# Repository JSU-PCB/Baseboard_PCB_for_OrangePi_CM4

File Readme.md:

# Baseboard PCB for OrangePi CM4

## 📌 Project Overview
This project documents the design and development of a custom baseboard for the Orange Pi CM4 compute module. It serves as a practical reference for a complete hardware design workflow, from initial schematic capture to PCB layout and manufacturing output. The goal is to share the experience and methodology of building a functional, production‑ready baseboard.

The project is developed in KiCad and cross‑referenced with Altium Designer for validation and advanced analysis. Both tools are used to ensure a comprehensive and reliable design flow.

## ⚠️ Disclaimer
This project is provided **"as is"** for educational and experimental purposes only. No warranty or guarantee is made regarding the correctness, completeness, or safety of the design. The authors accept **no responsibility or liability** for any damages, data loss, or injuries resulting from the use, assembly, or manufacture of this design. Users are solely responsible for verifying the suitability and accuracy of the design for their specific applications.

## 🔧 Contribution
Contributions are welcome! If you find a bug, have a suggestion, or want to help improve the design, please open an **Issue** or submit a **Pull Request**. All contributions must comply with the project's license and code of conduct.

## 📜 License
This hardware design is released under the **CERN Open Hardware Licence Version 2 – Permissive (CERN-OHL-P-2.0)**.  
You are free to use, study, modify, and distribute the design, provided you retain the copyright notice and disclaimer. Commercial use is permitted without the obligation to share proprietary modifications, though we encourage sharing improvements with the community.

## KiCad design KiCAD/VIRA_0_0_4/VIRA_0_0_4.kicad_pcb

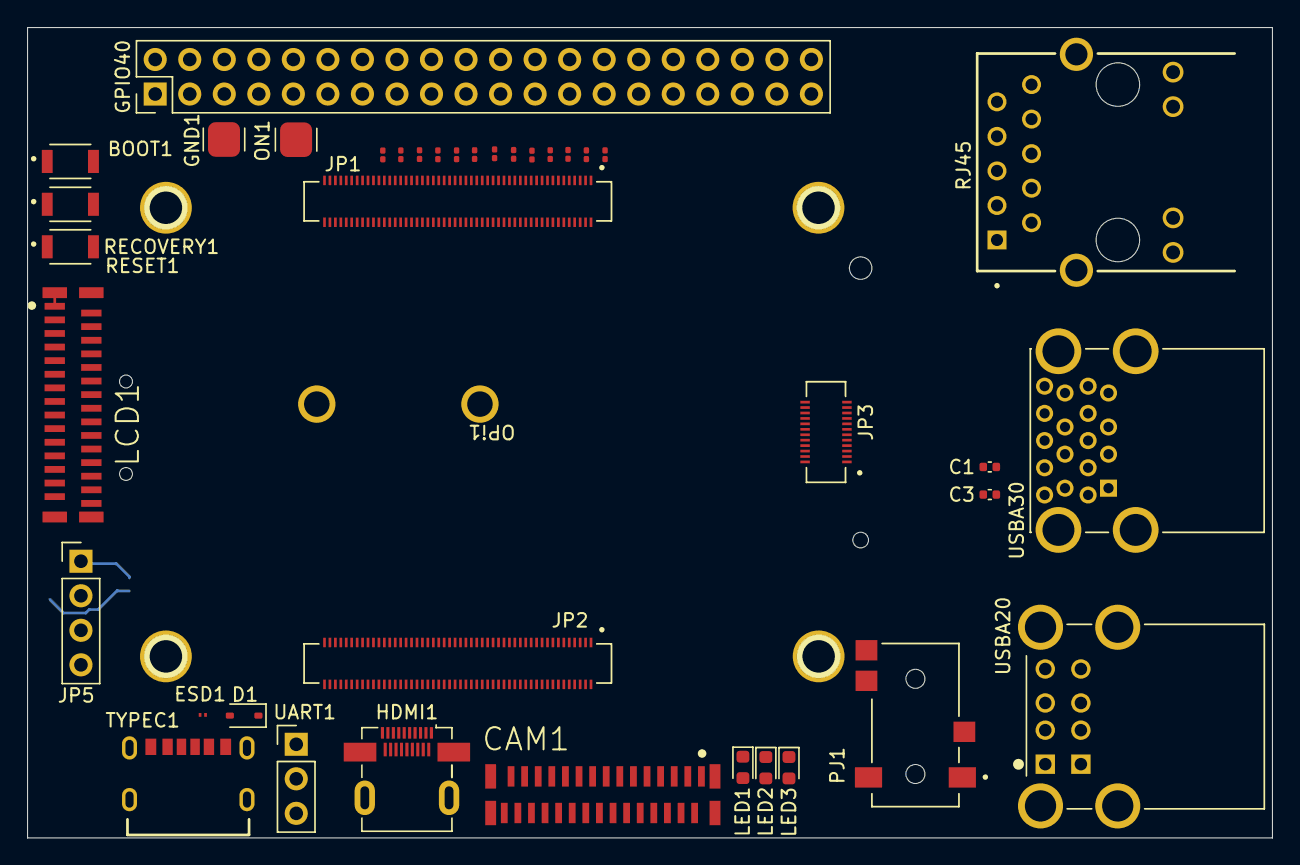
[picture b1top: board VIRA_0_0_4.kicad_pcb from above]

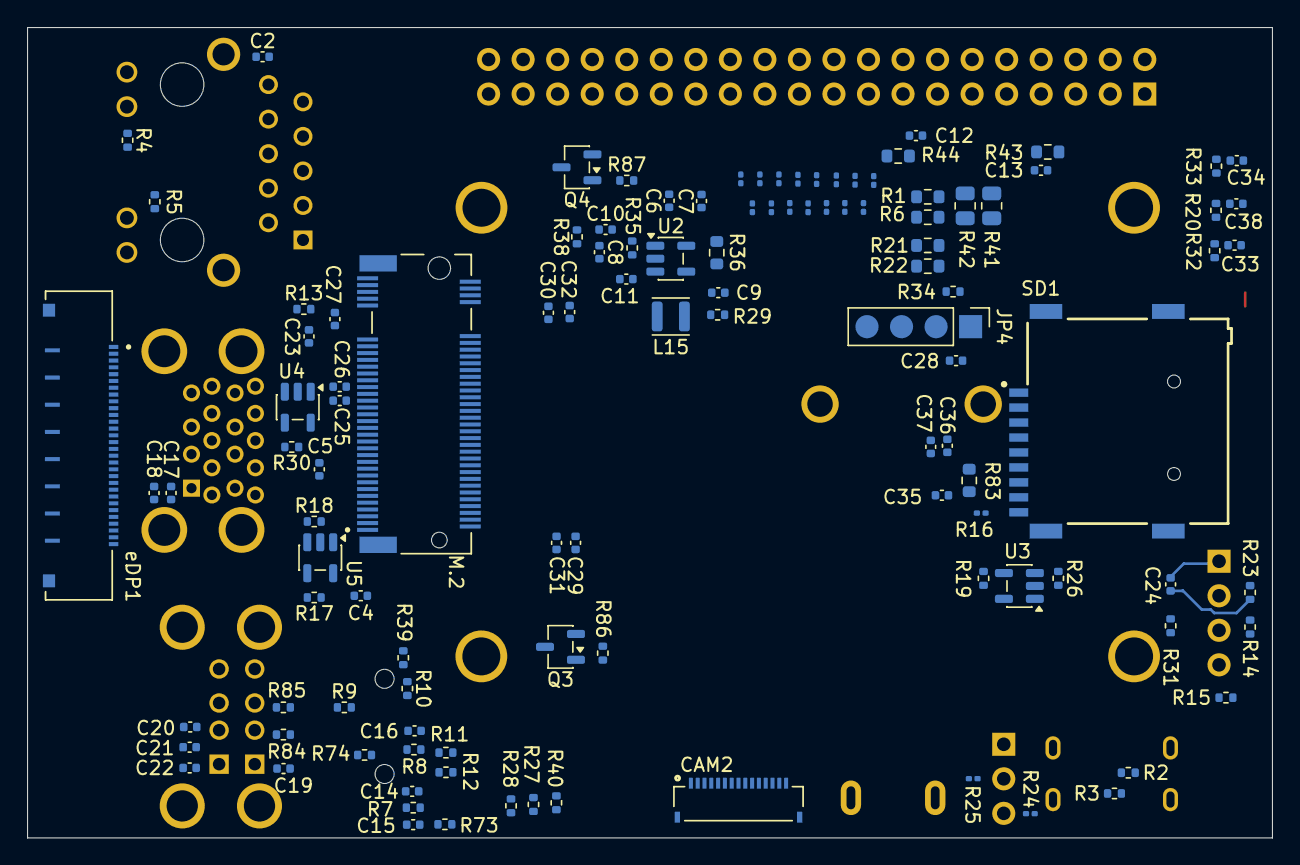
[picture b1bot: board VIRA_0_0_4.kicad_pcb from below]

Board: 6 copper layers, 91.6 x 59.6 mm, 153 parts (113 on the bottom side), 207 nets.

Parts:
BOOT1: SW_Omron_B3FS; SW_B3U-1000P
C1, C2, C3, C4, C5, C7, C8, C10, C15, C16, C18, C20, C22, C25, C26, C27, C31, C32, C33, C34, C35, C37, C38: 100nF; C_0402_1005Metric
C6, C11, C12, C13, C14, C17, C19, C21, C23, C24, C28, C29, C30, C36: 10uF; C_0402_1005Metric
C9: 22pF; C_0402_1005Metric
CAM1: FH12-30S-0.5SVA_54_; HIROSE_FH12-30S-0.5SVA
CAM2: FH19C-15S-0.5SH_10_; HRS_FH19C-15S-0.5SH_10_
D1: 1N5819; D_SOD-323
ESD1: PESD5V0H1BSFYL; DIO_PESD5V0H1BSFYL
GND1: GND; Pad
GPIO40: MTLW-120-06-G-D-160; PinHeader_2x20_P2.54mm_Vertical
HDMI1: 467652301; HDMI_Micro-D_Molex_46765-2xxx
JP1, JP2: DF40C-100DS-0.4V_51_; HIROSE_DF40C-100DS-0.4V_51_
JP3: DF40C-24DS-0.4V_51_; HIROSE_DF40C-24DS-0.4V_51_
JP4: HEADER 4; Pad SMD 1x4
JP5: HEADER 4; PinHeader_1x04_P2.54mm_Vertical
L15: 2.2uH; L_Wuerth_PMCI-252012
LCD1: FH12-30S-0.5SVA_54_; HIROSE_FH12-30S-0.5SVA
LED1: LED_RED; LED_0603_1608Metric
LED2: LED_GREEN; LED_0603_1608Metric
LED3: LED_BLUE; LED_0603_1608Metric
M.2: MDT420M03001; AMPHENOL_MDT420M03001
ON1: ON; Pad
OPi1: OpiCM4
PJ1: SJ2-35894B-SMT-TR; CUI_SJ2-35894B-SMT-TR
Q3, Q4: 2SK3018; SOT-23-3
R1, R6, R21: NC 0R; R_0603_1608Metric
R2, R3, R39: 5.1K; R_0402_1005Metric
R4, R5, R9, R10, R27, R28: 470R; R_0402_1005Metric
R7, R11, R73: 100K; R_0402_1005Metric
R8, R15, R23, R33, R34: 0R; R_0402_1005Metric
R12, R20, R32: 22R; R_0402_1005Metric
R13, R18, R26: 6K8; R_0402_1005Metric
R14, R31: 10K; R_0402_1005Metric
R16, R24, R25, R45, R46, R47, R49, R50, R54, R55, R56, R57, R59, R60, R61, R63, R64, R65, R66, R67, R68, R69, R70: 200R; R_0201_0603Metric
R17, R19, R30, R38: NC 10K; R_0402_1005Metric
R22, R36, R43, R44: 0R; R_0603_1608Metric
R29: 232K; R_0402_1005Metric
R35: 49.9K; R_0402_1005Metric
R40: 2K2; R_0402_1005Metric
R41, R42: 0R; R_0805_2012Metric
R48, R51, R52, R53, R58, R62, R71, R72: 47R; R_0201_0603Metric
R74: 2.2K; R_0402_1005Metric
R83: 1K; R_0603_1608Metric
R84, R85: 2R2; R_0402_1005Metric
R86, R87: 33K; R_0402_1005Metric
RECOVERY1: SW_Omron_B3FS; SW_B3U-1000P
RESET1: SW_Omron_B3FS; SW_B3U-1000P
RJ45: MGC005-2CD2C001H_REVA; GCT_MGC005-2CD2C001H_REVA
SD1: MEM2075-00-140-01-A; GCT_MEM2075-00-140-01-A
TYPEC1: USB4125-GF-A_REVA2; GCT_USB4125-GF-A_REVA2
U2: ETA3409/SY8089AAC; SOT-23-5
U3, U4, U5: SGM2590D; SOT-23-5
UART1: Conn_01x03; PinHeader_1x03_P2.54mm_Vertical
USBA20: USB_HOST; TE_5787745-2
USBA30: SS-52000-003; STEWART_SS-52000-003
eDP1: FH63S-30S-0.5SH; HRS_FH63S-30S-0.5SH

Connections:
/Page_3/CC1: R2.1, TYPEC1.A5 (CC1)
/Page_3/CC2: R3.1, TYPEC1.B5 (CC2)
BOOT-SW: JP1.93, R33.2
BT_nDIS: JP1.91, R6.2
CAMERA_PDN_L: CAM1.$21 (21), CAM1.$22 (22), CAM2.11, JP1.97
DIY_LED: JP1.21, eDP1.8
EDP_TX_AUXN: JP2.66, eDP1.21
EDP_TX_AUXP: JP2.64, eDP1.22
EDP_TX_D0N: JP2.60, eDP1.25
EDP_TX_D0P: JP2.58, eDP1.24
EDP_TX_D1N: JP2.54, eDP1.28
EDP_TX_D1P: JP2.52, eDP1.27
GND: BOOT1.2, C2.1, C4.2, C5.2, C6.2, C7.2, C8.2, C10.2, C11.2, C12.2, C13.2, C14.1, C15.2, C16.2, C17.2, C18.2, C19.2, C20.2, C21.2, C22.2, C23.2, C24.2, C27.2, C28.2, C29.2, C30.2, C31.2, C32.2, C33.2, C34.2, C35.2, C36.2, C37.2, C38.2, CAM1.31 (PADS), CAM1.32 (PADS), CAM1.33 (PADS), CAM1.34 (PADS), CAM1.$1 (1), CAM1.$2 (2), CAM1.$7 (7), CAM1.$8 (8), CAM1.$13 (13), CAM1.$14 (14), CAM1.$19 (19), CAM1.$20 (20), CAM2.1, CAM2.4, CAM2.7, CAM2.10, CAM2.SH1 (SHIELD), CAM2.SH2 (SHIELD), ESD1.2, GND1.1 (1_1), GPIO40.6, GPIO40.9, GPIO40.14, GPIO40.20, GPIO40.25, GPIO40.30, GPIO40.34, GPIO40.39, HDMI1.4 (TMDS_DATA2_SHIELD), HDMI1.7 (TMDS_DATA1_SHIELD), HDMI1.10 (TMDS_DATA0_SHIELD), HDMI1.13 (TMDS_CLOCK_SHIELD), HDMI1.16 (DDC/CEC_GROUND), HDMI1.SH (Shield), JP1.1, JP1.2, JP1.7, JP1.8, JP1.13, JP1.14, JP1.22, JP1.23, JP1.32, JP1.33, JP1.42, JP1.43, JP1.52, JP1.53, JP1.59, JP1.60, JP1.65, JP1.66, JP1.71, JP1.74, JP1.98, JP2.7, JP2.8, JP2.13, JP2.14, JP2.19, JP2.20, JP2.25, JP2.26, JP2.31, JP2.32, JP2.37, JP2.38, JP2.44, JP2.50, JP2.55, JP2.56, JP2.61, JP2.62, JP2.67, JP2.68, JP2.73, JP2.74, JP2.79, JP2.80, JP2.85, JP2.86, JP2.91, JP2.92, JP2.97, JP2.98, JP3.1, JP3.2, JP3.7, JP3.13, JP3.14, JP3.17, JP3.20, JP3.23, JP4.1, JP5.1, LCD1.31 (PADS), LCD1.32 (PADS), LCD1.33 (PADS), LCD1.34 (PADS), LCD1.$1 (1), LCD1.$2 (2), LCD1.$7 (7), LCD1.$8 (8), LCD1.$13 (13), LCD1.$14 (14), LCD1.$19 (19), LCD1.$20 (20), LCD1.$25 (25), LCD1.$26 (26), LED1.1 (K), M.2.1, M.2.3, M.2.9, M.2.15, M.2.21, M.2.27, M.2.33, M.2.39, M.2.45, M.2.51, M.2.57, M.2.69, M.2.71, M.2.73, M.2.75, M.2.S1 (Shield), M.2.S2 (Shield), Q3.2 (S), Q4.2 (S), R1.1, R2.2, R3.2, R6.1, R7.2, R8.2, R9.2, R10.2, R13.2, R18.2, R26.2, R35.2, RECOVERY1.2, RESET1.2, RJ45.SH1 (SHIELD), RJ45.SH2 (SHIELD), SD1.P6 (VSS), SD1.SH1 (SHIELD), SD1.SH2 (SHIELD), SD1.SH3 (SHIELD), SD1.SH4 (SHIELD), TYPEC1.A12 (GND), TYPEC1.B12 (GND), TYPEC1.S1 (SHIELD), TYPEC1.S2 (SHIELD), TYPEC1.S3 (SHIELD), TYPEC1.S4 (SHIELD), U2.2 (GND), U3.2 (GND), U4.2 (GND), U5.2 (GND), UART1.1, USBA20.4A (GND1), USBA20.4B (GND2), USBA20.S1 (SH), USBA20.S2 (SH), USBA20.S3 (SH), USBA20.S4 (SH), USBA30.4 (GND_1), USBA30.7 (GND_DRAIN_1), USBA30.13 (GND_2), USBA30.16 (GND_DRAIN_2), USBA30.SH1 (SHIELD), USBA30.SH2 (SHIELD), USBA30.SH3 (SHIELD), USBA30.SH4 (SHIELD), eDP1.10, eDP1.11, eDP1.12, eDP1.13, eDP1.15, eDP1.16, eDP1.20, eDP1.23, eDP1.26, eDP1.29, eDP1.G1 (GND), eDP1.G2 (GND), eDP1.G3 (GND), eDP1.G4 (GND), eDP1.G5 (GND), eDP1.G6 (GND), eDP1.G7 (GND), eDP1.G8 (GND), eDP1.S1 (GND), eDP1.S2 (GND)
GPIO0_C6-PWM7_IR: JP1.72, R14.2, R15.1
GPIO0_D0 (UART2_RX_M0): JP1.51, R25.2, R61.1
GPIO0_D1 (UART2_TX_M0): JP1.55, R24.2, R60.1
GPIO1_A0 (I2C3_SDA_M0): CAM2.14, JP1.36, R54.2
GPIO1_A1 (I2C3_SCL_M0): CAM2.13, JP1.35, R68.1
GPIO3_C6 (I2S1_MCLK_M1: JP1.50, R48.2
GPIO3_C7 (I2S1_SCLK_M1: JP1.49, R62.1
GPIO3_D0 (I2S1_LRCK_M1): JP1.26, R58.2
GPIO3_D1 (I2S1_SDO_M1): JP1.25, R72.1
GPIO3_D2 (I2S1_SDI_M1): JP1.27, R71.1
GPIO3_D4: JP1.30, R56.2
GPIO3_D5: JP1.29, R70.1
GPIO3_D7: JP1.28, R57.2
GPIO4_A0: JP1.48, R49.2
GPIO4_A1: JP1.45, R64.1
GPIO4_A2: JP1.46, R50.2
GPIO4_A3: JP1.47, R63.1
GPIO4_A4: JP1.41, R65.1
GPIO4_A5: JP1.34, R55.2
GPIO4_A6 (SPI3_CS0_M0): JP1.39, R66.1
GPIO4_A7 (SPI3_CS1_M0): JP1.37, R67.1
GPIO4_B0 (SPI3_MISO_M0): JP1.40, R52.2
GPIO4_B2 (SPI3_MOSI_M0): JP1.44, R51.2
GPIO4_B3 (SPI3_CLK_M0): JP1.38, R53.2
GPIO4_B4 (I2C2_SDA_M1): JP1.58, R45.2
GPIO4_B5 (I2C2_SCL_M1): JP1.56, R46.2
GPIO4_C0(PWM11_IR_M1): JP1.31, R69.1
GPIO4_C3/PWM15_IR_M1: JP1.54, R47.2
HDMI_CEC_PORT: HDMI1.15 (CEC), JP2.51
HDMI_TX0N: HDMI1.11 (TMDS_DATA0-), JP2.84
HDMI_TX0P: HDMI1.9 (TMDS_DATA0+), JP2.82
HDMI_TX1N: HDMI1.8 (TMDS_DATA1-), JP2.78
HDMI_TX1P: HDMI1.6 (TMDS_DATA1+), JP2.76
HDMI_TX2N: HDMI1.5 (TMDS_DATA2-), JP2.72
HDMI_TX2P: HDMI1.3 (TMDS_DATA2+), JP2.70
HDMI_TXCLKN: HDMI1.14 (TMDS_CLOCK-), JP2.90
HDMI_TXCLKP: HDMI1.12 (TMDS_CLOCK+), JP2.88
HDMI_TXDDC_SCL_PORT: HDMI1.17 (SCL), JP2.100
HDMI_TXDDC_SDA_PORT: HDMI1.18 (SDA), JP2.99
HDMI_TX_HPD_PORT: HDMI1.1 (HOT_PLUG_DETECT), JP2.53
HPL_OUT: JP3.6, PJ1.2, R10.1
HPR_OUT: JP3.4, PJ1.3, R9.1
HP_DET_L: C16.1, JP3.15, R11.1, R39.2
HP_SNS: JP3.8, PJ1.4, R8.1
I2C1_SCL_M0: CAM1.$25 (25), CAM1.$26 (26), JP1.80, LCD1.$21 (21)
I2C1_SDA_M0: CAM1.$27 (27), CAM1.$28 (28), JP1.82, LCD1.$23 (23)
MIC1_IN: JP3.10, PJ1.1, R73.1, R74.1
MIPI_CSI_RX_CLK0N: CAM1.$15 (15), CAM1.$16 (16), JP2.27
MIPI_CSI_RX_CLK0P: CAM1.$17 (17), CAM1.$18 (18), JP2.29
MIPI_CSI_RX_CLK1N: CAM2.8, JP2.40
MIPI_CSI_RX_CLK1P: CAM2.9, JP2.42
MIPI_CSI_RX_D0N: CAM1.$3 (3), CAM1.$4 (4), JP2.15
MIPI_CSI_RX_D0P: CAM1.$5 (5), CAM1.$6 (6), JP2.17
MIPI_CSI_RX_D1N: CAM1.$9 (9), CAM1.$10 (10), JP2.21
MIPI_CSI_RX_D1P: CAM1.$11 (11), CAM1.$12 (12), JP2.23
MIPI_CSI_RX_D2N: CAM2.2, JP2.28, JP2.33
MIPI_CSI_RX_D2P: CAM2.3, JP2.30, JP2.35
MIPI_CSI_RX_D3N: CAM2.5, JP2.34, JP2.39
MIPI_CSI_RX_D3P: CAM2.6, JP2.36, JP2.41
MIPI_DSI_TX1_CLKN: JP2.87, LCD1.$9 (9), LCD1.$10 (10)
MIPI_DSI_TX1_CLKP: JP2.89, LCD1.$11 (11), LCD1.$12 (12), R59.2
MIPI_DSI_TX1_D0N: JP2.75, LCD1.$15 (15), LCD1.$16 (16)
MIPI_DSI_TX1_D0P: JP2.77, LCD1.$17 (17), LCD1.$18 (18)
MIPI_DSI_TX1_D1N: JP2.81, LCD1.$3 (3)
MIPI_DSI_TX1_D1P: JP2.83, LCD1.$5 (5)
unnamed: BOOT1.1, C34.1, R33.1
unnamed: C14.2, R12.1, R74.2
unnamed: C25.2, M.2.47
unnamed: C26.2, M.2.49
unnamed: C33.1, R32.1, RESET1.1
unnamed: C38.1, R20.1, RECOVERY1.1
unnamed: GPIO40.1, GPIO40.17, R44.1
unnamed: GPIO40.2, GPIO40.4, R43.1
unnamed: GPIO40.3, R45.1
unnamed: GPIO40.5, R46.1
unnamed: GPIO40.7, R47.1
unnamed: GPIO40.8, R60.2
unnamed: GPIO40.10, R61.2
unnamed: GPIO40.11, R48.1
unnamed: GPIO40.12, R62.2
unnamed: GPIO40.13, R49.1
unnamed: GPIO40.15, R50.1
unnamed: GPIO40.16, R63.2
unnamed: GPIO40.18, R64.2
unnamed: GPIO40.19, R51.1
unnamed: GPIO40.21, R52.1
unnamed: GPIO40.22, R65.2
unnamed: GPIO40.23, R53.1
unnamed: GPIO40.24, R66.2
unnamed: GPIO40.26, R67.2
unnamed: GPIO40.27, R54.1
unnamed: GPIO40.28, R68.2
unnamed: GPIO40.29, R55.1
unnamed: GPIO40.31, R56.1
unnamed: GPIO40.32, R69.2
unnamed: GPIO40.33, R57.1
unnamed: GPIO40.35, R58.1
unnamed: GPIO40.36, R70.2
unnamed: GPIO40.37, R59.1
unnamed: GPIO40.38, R71.2
unnamed: GPIO40.40, R72.2
unnamed: D1.C, HDMI1.19 (+5V_POWER)
unnamed: C28.1, JP4.2, R34.1
unnamed: C24.1, JP5.2, R23.2
unnamed: JP5.3, R31.2
unnamed: JP5.4, R15.2
unnamed: LED1.2 (A), R40.1
unnamed: LED2.2 (A), R27.1
unnamed: LED2.1 (K), Q4.3 (D)
unnamed: LED3.2 (A), R28.1
unnamed: LED3.1 (K), Q3.3 (D)
unnamed: M.2.10, R86.1
unnamed: PJ1.10, R39.1
unnamed: Q3.1 (G), R86.2
unnamed: Q4.1 (G), R87.2
unnamed: R4.1, RJ45.13
unnamed: R5.1, RJ45.11
unnamed: C2.2, RJ45.10 (GND)
unnamed: R16.2, SD1.P9 (CD)
unnamed: C8.1, R38.1, U2.1 (EN)
unnamed: C9.2, R29.2, R35.1, U2.5 (FB/OUT)
unnamed: L15.1, U2.3 (LX)
unnamed: R19.2, U3.4 (EN)
unnamed: R26.1, U3.3 (FLAG)
unnamed: R30.2, U4.4 (EN)
unnamed: R13.1, U4.3 (FLAG)
unnamed: R17.2, U5.4 (EN)
unnamed: R18.1, U5.3 (FLAG)
unnamed: R25.1, UART1.2
unnamed: R24.1, UART1.3
unnamed: R85.2, USBA20.3B (D2+)
unnamed: R84.2, USBA20.2B (D2-)
unnamed: C3.1, USBA30.18 (SSTX+_2)
unnamed: C1.1, USBA30.17 (SSTX-_2)
unnamed: eDP1.2, eDP1.3, eDP1.5
PCIE20_CLKREQn_3V3_L: JP2.2, M.2.52
PCIE20_PERSTn_3V3_L: JP2.9, M.2.50
PCIE20_REFCLK_N: JP2.12, M.2.53
PCIE20_REFCLK_P: JP2.10, M.2.55
PCIE20_RXN: JP2.18, M.2.41
PCIE20_RXP: JP2.16, M.2.43
PCIE20_TXN: C25.1, JP2.24
PCIE20_TXP: C26.1, JP2.22
PCIE20_WAKEn_3V3_L: JP2.4, M.2.54
PHY1_LED1: JP1.17, RJ45.14
PHY1_LED2: JP1.15, RJ45.12
PHY1_MDI0+: JP1.12, RJ45.1 (TD1+)
PHY1_MDI0-: JP1.10, RJ45.2 (TD1-)
PHY1_MDI1+: JP1.4, RJ45.3 (TD2+)
PHY1_MDI1-: JP1.6, RJ45.4 (TD2-)
PHY1_MDI2+: JP1.11, RJ45.5 (TD3+)
PHY1_MDI2-: JP1.9, RJ45.6 (TD3-)
PHY1_MDI3+: JP1.3, RJ45.7 (TD4+)
PHY1_MDI3-: JP1.5, RJ45.8 (TD4-)
PMIC_PWRON: JP1.99, ON1.1 (1_1)
RESETn: JP1.92, R32.2
SARADC_VIN1: C15.1, JP1.70, R7.1, R73.2
SARADC_VIN2: JP1.96, JP4.3
SARADC_VIN3: JP1.94, JP4.4
SDMMC0_CLK: JP1.57, SD1.P5 (CLK)
SDMMC0_CMD: JP1.62, SD1.P3 (CMD)
SDMMC0_D0: JP1.63, SD1.P7 (DAT0)
SDMMC0_D1: JP1.67, SD1.P8 (DAT1)
SDMMC0_D2: JP1.69, SD1.P1 (DAT2)
SDMMC0_D3: JP1.61, SD1.P2 (CD/DAT3)
SDMMC0_DET_L: JP1.76, R16.1, R83.2
SD_PWR_ON: JP1.75, eDP1.9
SW_RECOVERY: JP1.68, R20.2
USB2-VBUS: C17.1, C18.1, C19.1, C20.1, C21.1, C22.1, U5.1 (VOUT1), USBA20.1A (VBUS1), USBA20.1B (VBUS2), USBA30.1 (VBUS_1)
USB2_HOST2_DN: JP3.9, USBA20.2A (D1-)
USB2_HOST2_DP: JP3.11, USBA20.3A (D1+)
USB2_HOST3_DN: JP3.3, USBA30.2 (D-_1)
USB2_HOST3_DP: JP3.5, USBA30.3 (D+_1)
USB3-VBUS: C23.1, C27.1, U4.1 (VOUT1), USBA30.10 (VBUS_2)
USB3_HOST1_DN: JP3.19, USBA30.11 (D-_2)
USB3_HOST1_DP: JP3.21, USBA30.12 (D+_2)
USB3_HOST1_SSRXN: JP3.24, USBA30.14 (SSRX-_2)
USB3_HOST1_SSRXP: JP3.22, USBA30.15 (SSRX+_2)
USB3_HOST1_SSTXN: C1.2, JP3.16
USB3_HOST1_SSTXP: C3.2, JP3.18
USB_OTG0_DN: JP2.3, R84.1
USB_OTG0_DP: JP2.5, R85.1
VCC1V8: JP1.88, JP1.90
VCC3V3_PCIE: C6.1, C7.1, C9.1, L15.2, R29.1, R36.2
VCC3V3_PCIE30: C29.1, C30.1, C31.1, C32.1, M.2.2, M.2.4, M.2.12, M.2.14, M.2.16, M.2.18, M.2.70, M.2.72, M.2.74, R28.2, R36.1
VCC3V3_SYS: JP1.84, JP1.86, R42.1
VCC5V0_SYS: JP1.77, JP1.79, JP1.81, JP1.83, JP1.85, JP1.87, R41.1
VCCIO6: JP1.78, R21.2, R22.2
VCC_3V3: C12.1, C35.1, CAM1.$29 (29), CAM1.$30 (30), CAM2.15, LCD1.$27 (27), LCD1.$28 (28), LCD1.$29 (29), LCD1.$30 (30), R4.2, R5.2, R11.2, R12.2, R14.1, R19.1, R22.1, R27.2, R31.1, R34.2, R40.2, R42.2, R44.2, RJ45.9 (VCC), U3.5 (IN), eDP1.18, eDP1.19
VCC_5V: C4.1, C5.1, C10.1, C11.1, C13.1, D1.A, ESD1.1, R17.1, R23.1, R30.1, R38.2, R41.2, R43.2, TYPEC1.A9 (VBUS), TYPEC1.B9 (VBUS), U2.4 (VIN), U4.5 (IN), U5.5 (IN), eDP1.4
VCC_SD: C36.1, C37.1, R83.1, SD1.P4 (VDD), U3.1 (VOUT1)
WL_nDIS: JP1.89, R1.2
WORK_LED: JP1.95, R87.1
nEXTRST: JP1.100, eDP1.14
